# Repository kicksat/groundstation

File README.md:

groundstation
=============

A GNURadio-based ground station receiver for the Sprite spacecraft.

# Installation

    $ mkdir -p gr-sprite/build && cd gr-sprite/build
    $ cmake ..
    $ make
    $ make install

# Usage

Record I/Q samples using your favorite SDR at 437 MHz. There are GRC flowgraphs
available to do the same. For example, to use the rtl-sdr recorder:

    $ gnuradio-companion gr-sprite/examples/SpriteRecorder_RTL.grc

Then, decode Sprite transmissions with:

    $ gnuradio-companion gr-sprite/examples/SpriteReceiver2.grc

To decode the samples you recorded, disable the rtl-sdr block and enable the
File Source and Throttle.

# License

[Creative Commons Attribution-ShareAlike 4.0 International](https://creativecommons.org/licenses/by-sa/4.0/)

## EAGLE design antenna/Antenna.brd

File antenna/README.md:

# antenna

This is the antenna board for KickSat-2. It is a V-dipole built into the bottom solar panel of the satellite.

# License

[Creative Commons Attribution-ShareAlike 4.0 International](https://creativecommons.org/licenses/by-sa/4.0/)

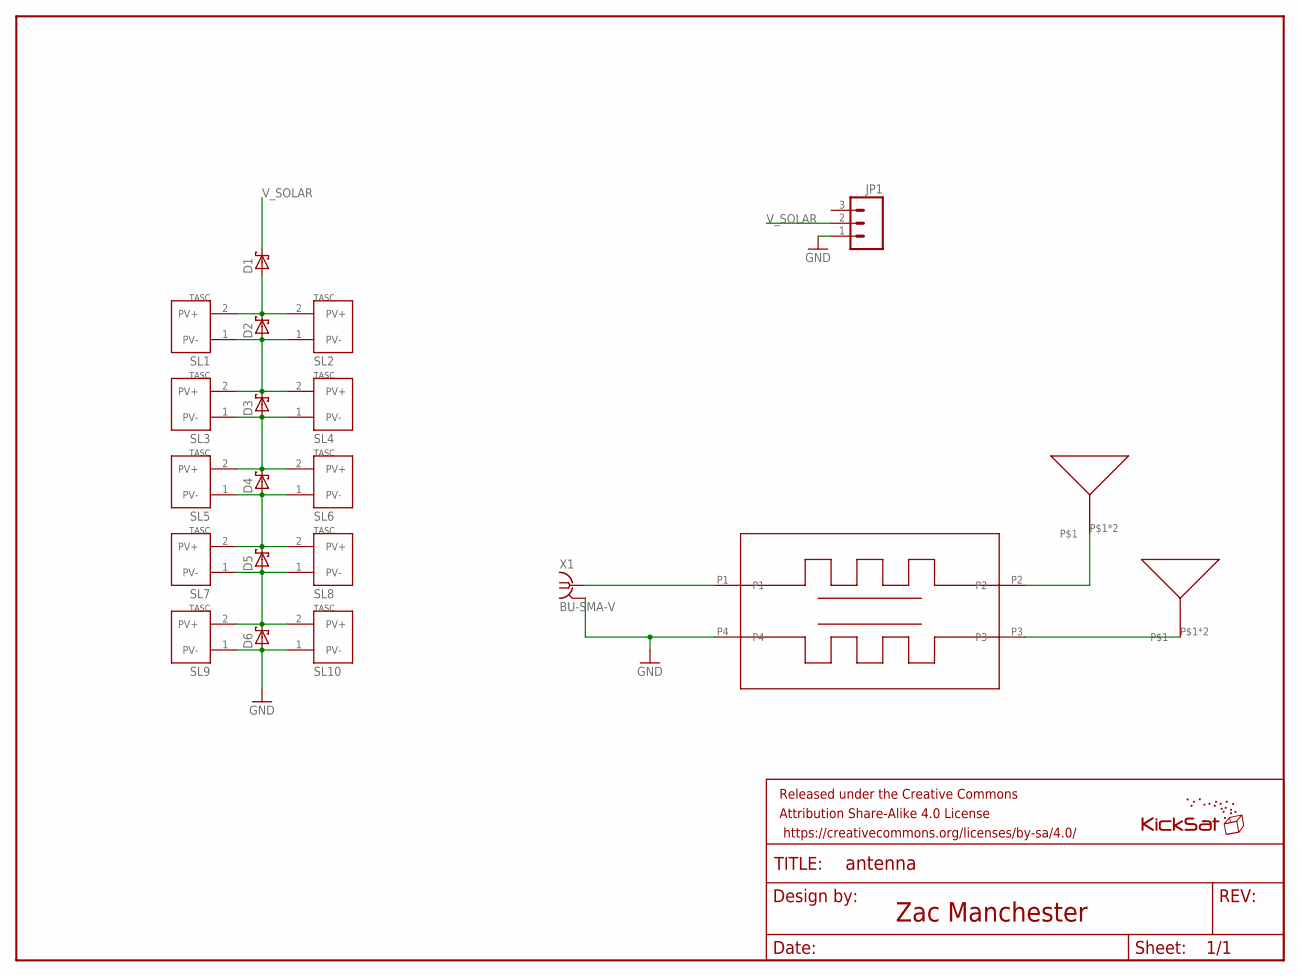
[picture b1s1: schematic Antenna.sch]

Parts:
B1: BALUN
D1, D2, D3, D4, D5, D6: SB_DIODE
FRAME1: FRAME-LETTER; CREATIVE_COMMONS
JP1: M03POLAR_LOCK; MOLEX-1X3_LOCK
SL1, SL2, SL3, SL4, SL5, SL6, SL7, SL8, SL9, SL10: SOLAR_CELL
U$1, U$2: TAPEANTENNA
U$3: KICKSAT_LOGO
X1: BU-SMA-V

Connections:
GND: B1.P4, D6.POS, JP1.1, SL9.1 (PV-), SL10.1 (PV-), X1.2, X1.3 (2), X1.4 (2), X1.5 (2)
unnamed: B1.P1, X1.1
unnamed: D1.POS, D2.NEG, SL1.2 (PV+), SL2.2 (PV+)
unnamed: D3.POS, D4.NEG, SL3.1 (PV-), SL4.1 (PV-), SL5.2 (PV+), SL6.2 (PV+)
unnamed: D4.POS, D5.NEG, SL5.1 (PV-), SL6.1 (PV-), SL7.2 (PV+), SL8.2 (PV+)
unnamed: D2.POS, D3.NEG, SL1.1 (PV-), SL2.1 (PV-), SL3.2 (PV+), SL4.2 (PV+)
unnamed: D5.POS, D6.NEG, SL7.1 (PV-), SL8.1 (PV-), SL9.2 (PV+), SL10.2 (PV+)
RFN: B1.P2, U$1.P$1, U$1.P$2
RFP: B1.P3, U$2.P$1, U$2.P$2
V_SOLAR: D1.NEG, JP1.2

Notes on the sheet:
Zac Manchester

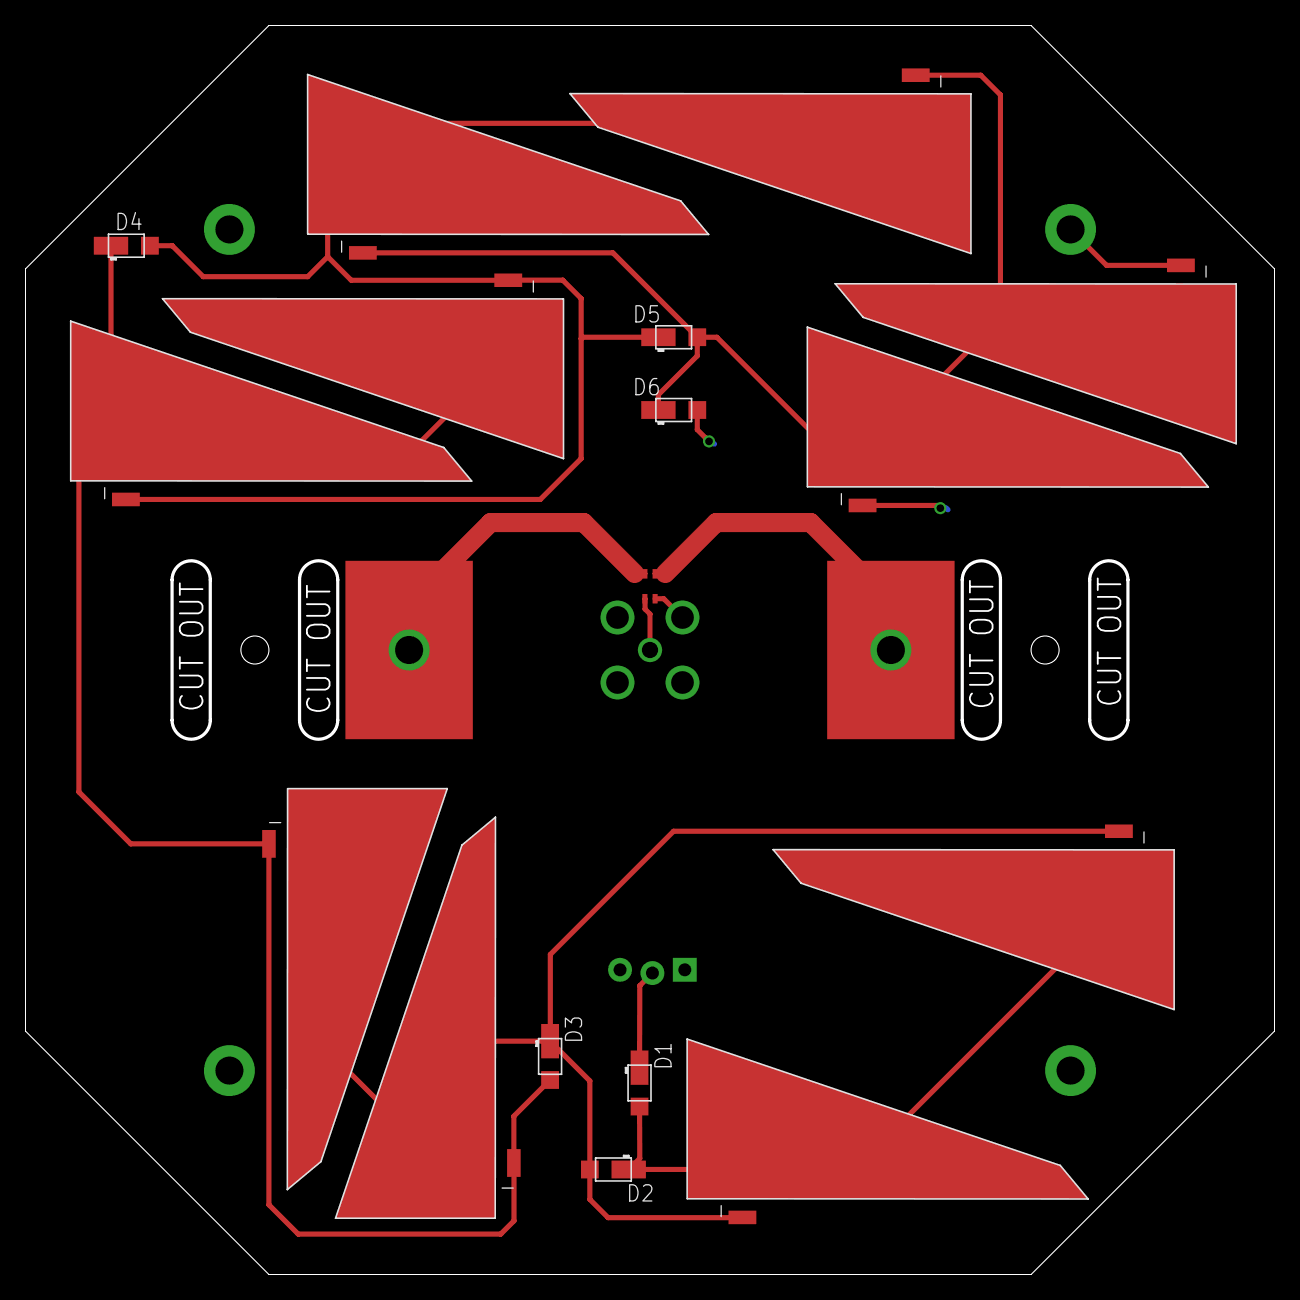
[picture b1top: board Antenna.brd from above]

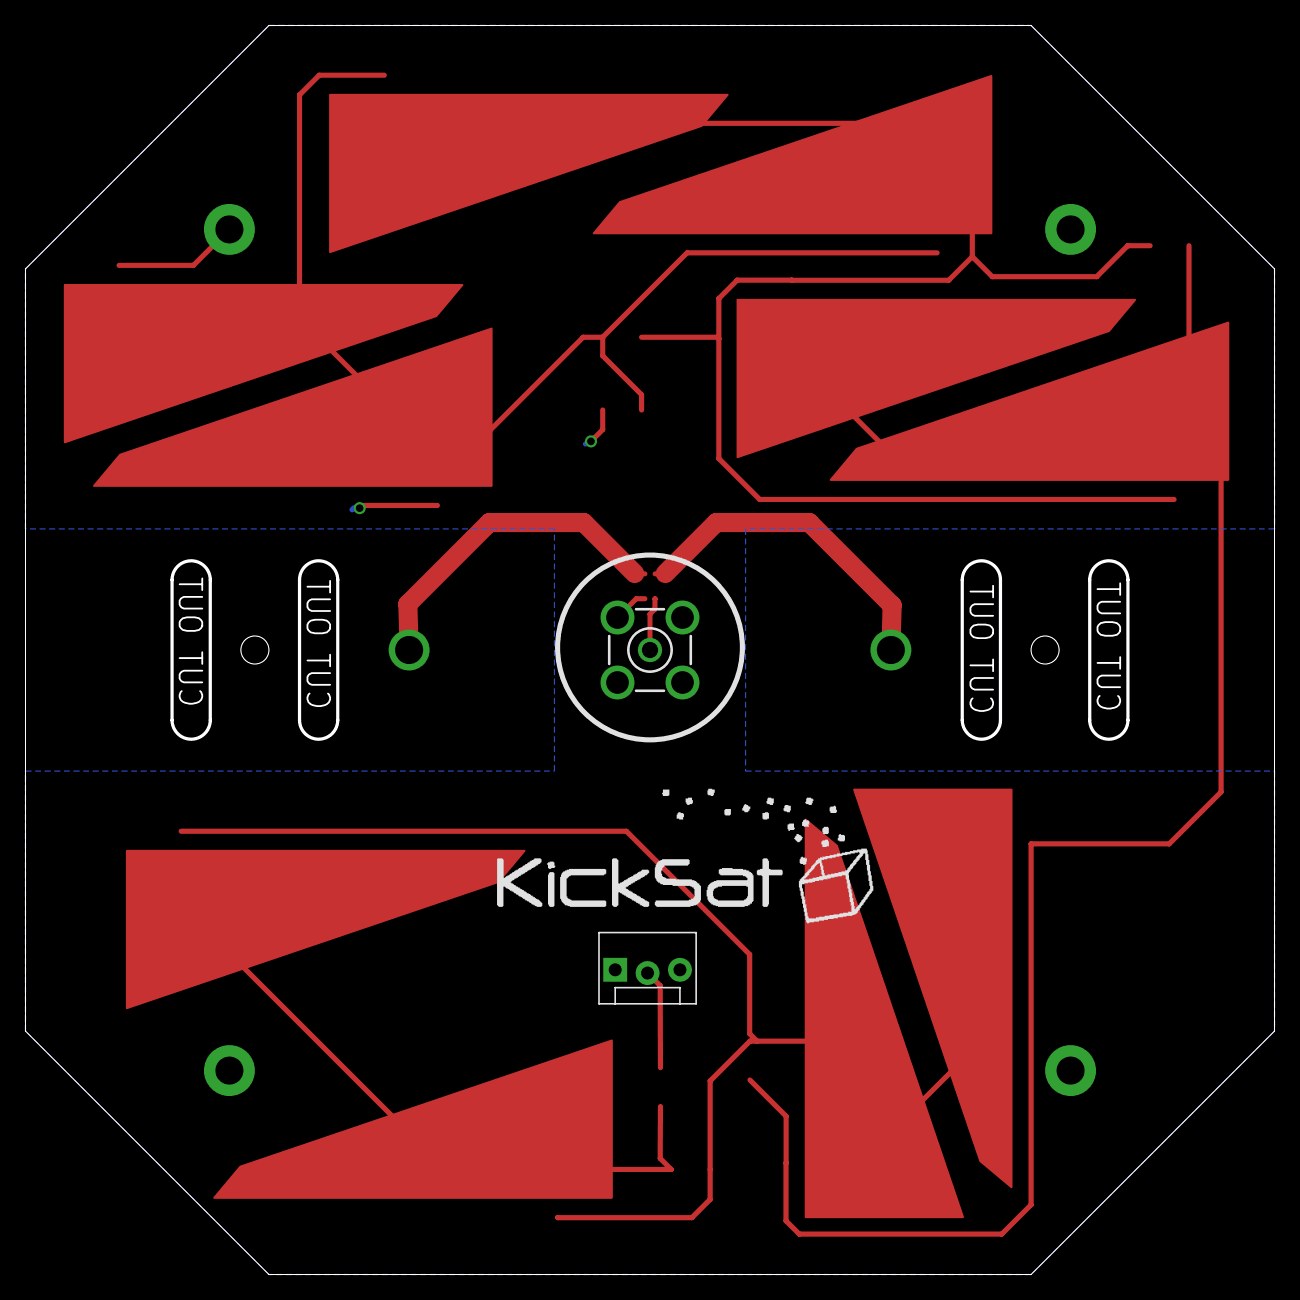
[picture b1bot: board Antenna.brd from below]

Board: 2 copper layers, 98.0 x 98.0 mm, 23 parts (3 on the bottom side), 10 nets.

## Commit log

2014-06-02 Initial move
2014-09-09 Updated install script
2015-01-21 Added window size input to decimator block
2015-03-19 New complex decoder
2015-03-19 Debugging new decoder
2015-03-19 Bug fix in new decoder
2015-03-19 New decoder working
2015-03-19 Added threshold parameter to decoder block
2015-03-20 Code refactoring in new decoder
2015-05-01 Some tweaks for better BER performance
2015-11-10 Updated link budget
2016-06-25 Updated install script for Ubuntu 16.04
2017-05-14 Putting together a special receiver
2017-05-14 A tweaked correlator + receiver
2017-05-14 Updated receiver
2017-05-14 Changed to HackRF
2017-07-03 Updated .gitignore
2017-07-03 Decoder working on recordings from Delft
2018-07-20 Set theme jekyll-theme-midnight
2018-07-20 reorganized
2018-07-22 Add pyc to gitignore
2018-07-22 Fix complex literal
2018-08-02 Create temp
2018-08-02 updated folder names
2018-09-10 Add CMake build directory to gitignore
2018-09-10 Move GRC examples to where they belong
2018-09-10 Remove old, broken receivers
2018-09-14 Added Arduino sketch for controlling amp via serial
2018-09-14 Added python script to control arduino
2018-09-24 Added over temperature monitoring

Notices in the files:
parts and their libraries:
SparkFun-Connectors: Licensing: Creative Commons ShareAlike 4.0 International - https://creativecommons.org/licenses/by-sa/4.0
SparkFun-Aesthetics: Released under the Creative Commons Attribution Share-Alike 4.0 License
SparkFun-Aesthetics: Released under the Creative Commons
